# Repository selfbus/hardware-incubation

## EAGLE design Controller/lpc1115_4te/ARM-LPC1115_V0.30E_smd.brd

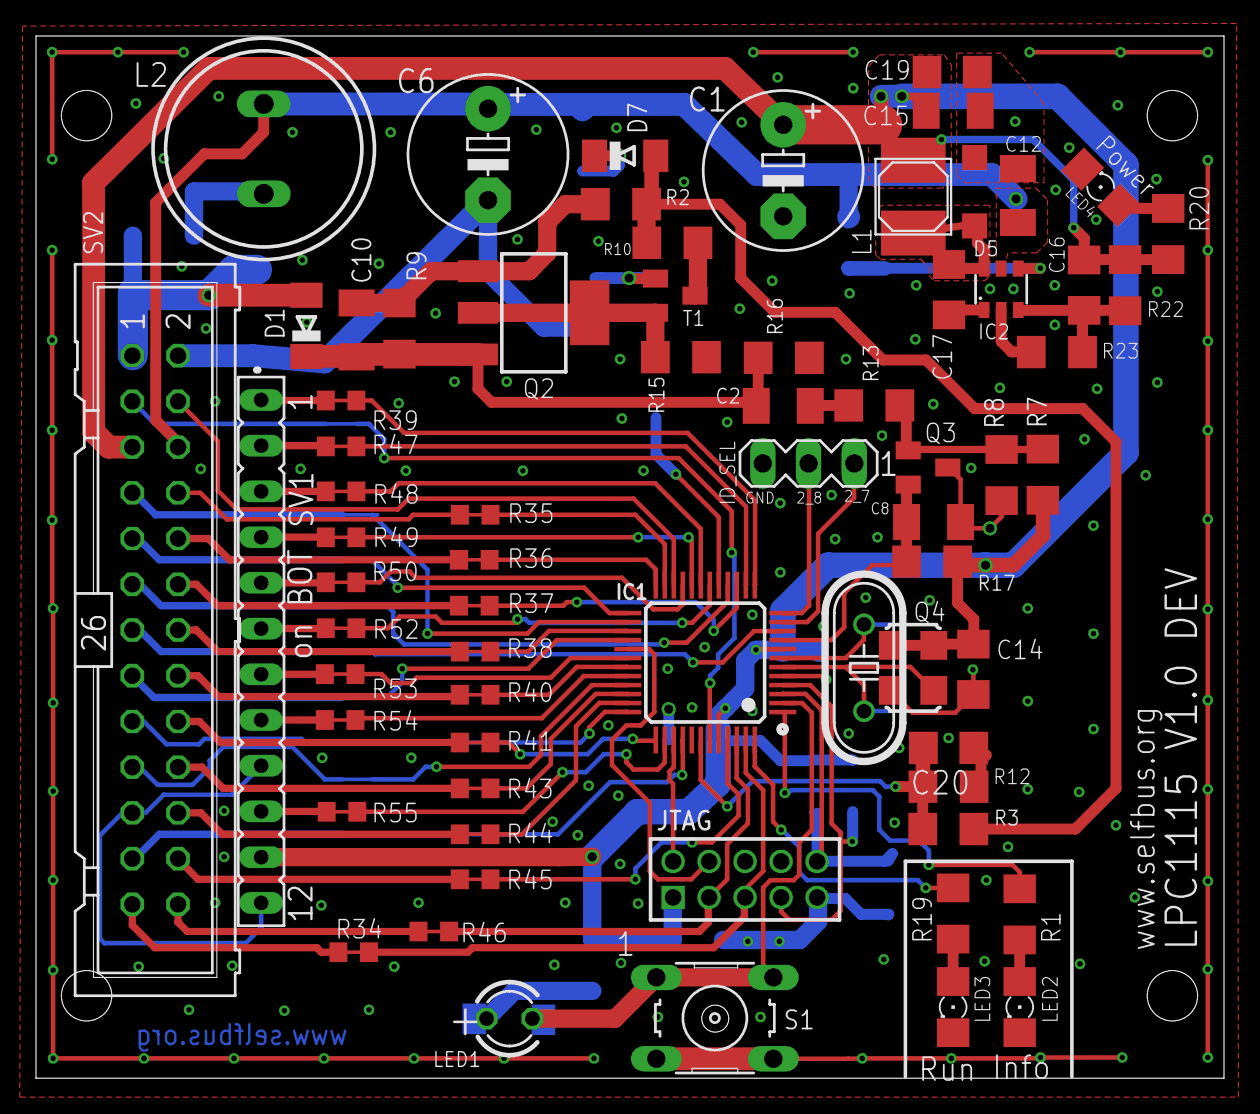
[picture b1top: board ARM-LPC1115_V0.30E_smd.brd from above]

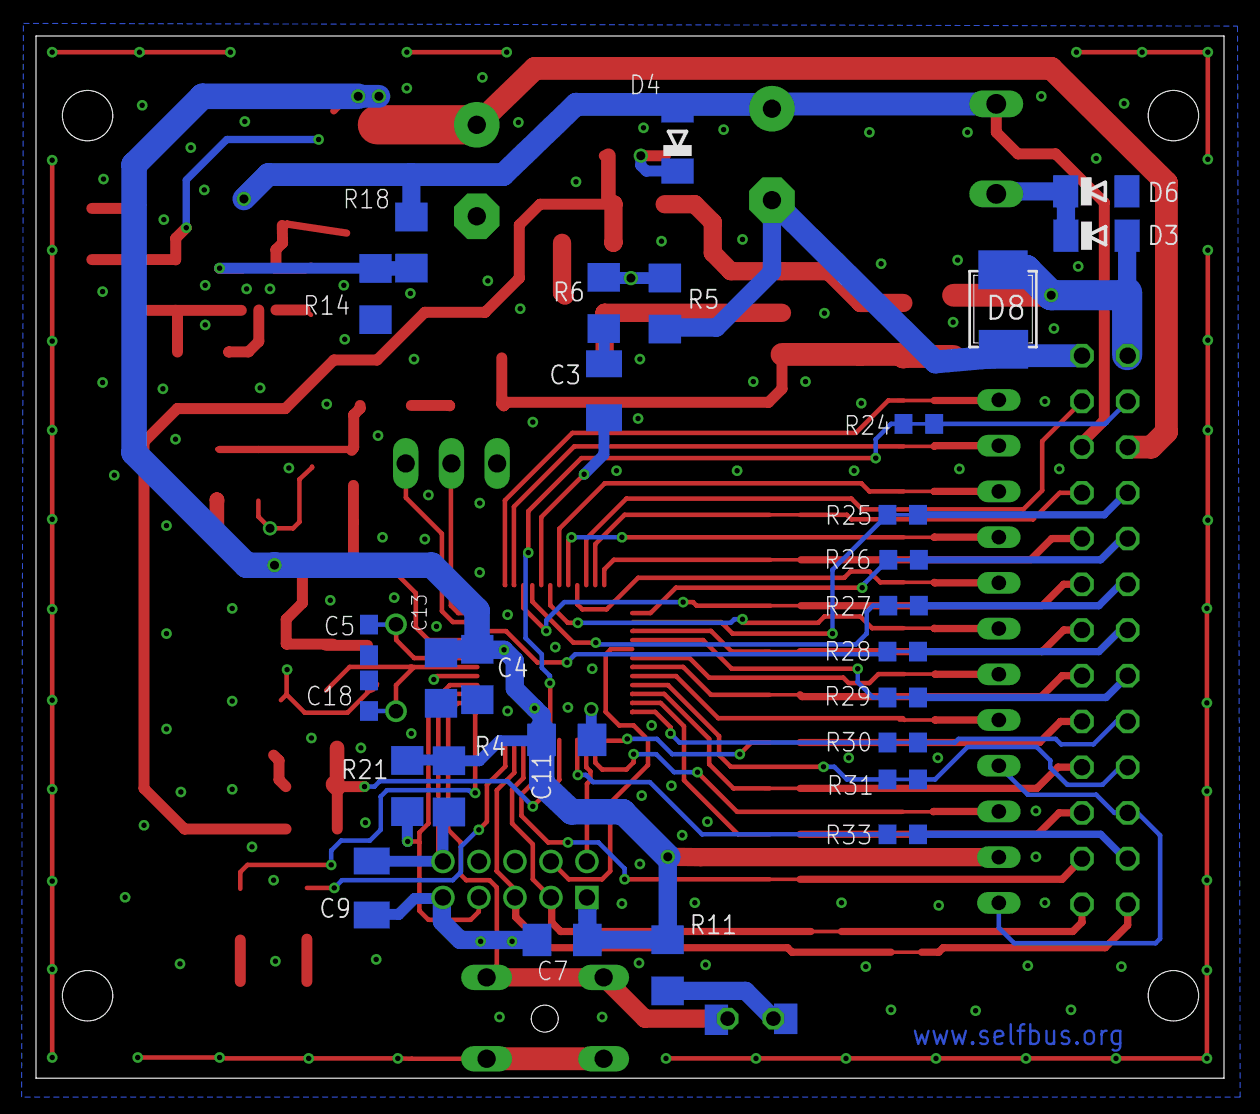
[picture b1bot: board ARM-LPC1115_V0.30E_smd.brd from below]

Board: 2 copper layers, 66.0 x 57.9 mm, 97 parts (28 on the bottom side), 96 nets.

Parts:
C1: 100µ / 10V; E5-8,5
C2: 100n; C1206K
C3, C9, C10: 10n; C1206K
C4, C14, C19: 10n; C1206
C5, C18: 18p; C0603
C6: 100µ / 50V; E5-8,5
C7, C11, C13: 100n; C1206
C8: 100p; C1206K
C12: 4.7µF/50V; C1206K
C15: 10µ / 10V; C1206K
C16: 270n; C1206
C17: 15nF; C1206
C20: 1n; C1206
D1, D3, D4, D6: 1N4148; MINIMELF
D5: RB060M-60; SOD123
D7: 7V5; MINIMELF
D8: SMB
IC1: LPC1115; LQFP48
IC2: BD9G101; SOT23-6
JTAG: J; 2X05M
L1: 6.8µH; PIS2812
L2: 150mH; SD12_1000
LED1: red; LED3MM
LED2: yellow; 1206
LED3: green; 1206
LED4: 1206
Q2: BCP52; SOT223
Q3: BC856; SOT23-BEC
Q4: 12MHz; ASF
R1, R2, R9, R11, R19, R20: 1k; R1206
R3: 91k; R1206
R4, R5, R16, R21: 100k; R1206
R6: 5k6; R1206
R7: 82k; R1206
R8: 47k; R1206
R10: 2k2; R1206
R12, R13, R17: 10k; R1206
R14: 43k; R1206
R15: 5R6; R1206
R18: 390k; R1206
R22: 2k4; R1206
R23: 680R; R1206
R24, R25, R26, R27, R28, R29, R30, R31, R33, R34, R35, R36, R37, R38, R39, R40, R41, R43, R44, R45, R46, R47, R48, R49, R50, R52, R53, R54, R55: R0603_BRIDGE
S1: Prog; B3F-10XX
SV1: LT; FE12
SV2: A; ML26
SV3: ID_SEL; MA03-1
T1: BC547C; SOT23
XTAL1: 12MHz; HC49/S

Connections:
$IO1: R25.2, SV2.7
$IO3: R26.2, SV2.9
$PWM: R24.2, SV2.3
$SDA: R27.2, SV2.11
APROG: IC1.22, SV2.4
BUS_V: C20.2, IC1.42, R3.2, R12.1
DRAIN: C2.1, C10.1, D1.C, Q2.3, R9.1, R16.2
EIB+: D1.A, D3.A, D8.1, SV2.1
EIB_DC: C6.+, C12.2, D4.A, IC2.5, L2.2, R18.1, SV2.6
EIB_IN: C8.2, IC1.9, Q3.E, R17.1
EIB_OUT: C3.2, IC1.17
GND: C1.-, C4.1, C5.1, C6.-, C7.1, C8.1, C9.1, C11.1, C12.1, C13.1, C14.2, C15.1, C18.1, C19.1, C20.1, D5.A, D6.A, D8.2, IC1.5, IC1.41, IC2.2, JTAG.9, LED2.C, LED3.C, LED4.C, Q3.C, Q4.2, R5.2, R8.1, R12.2, R14.2, R15.1, R16.1, R23.1, S1.1, S1.2, SV1.9, SV1.12, SV2.2, SV2.21, SV3.3
ID1: IC1.11, SV3.1
ID2: IC1.12, SV3.2
IO1: IC1.26, R25.1
IO2: IC1.23, R35.2
IO3: IC1.25, R26.1
IO4: IC1.24, R36.2
IO5: IC1.10, R28.1
IO6: IC1.27, R38.2
IO7: IC1.28, R29.1
IO8: IC1.31, R40.2
IO9: IC1.33, R31.1
IO10: IC1.34, R43.2
IO11: IC1.35, R44.2
IO12: IC1.40, R33.1
IO13: IC1.45, R45.2
IO14: IC1.47, JTAG.5, R34.1
IO15: IC1.46, JTAG.3, R46.2
ISP_EN: IC1.4, JTAG.7, R21.1
LT1: IC1.13, R39.1
LT2: IC1.14, R47.1
LT3: IC1.19, R48.1
LT4: IC1.20, R49.1
LT5: IC1.21, R50.1
LT6: IC1.18, R52.1
LT7: IC1.30, R53.1
LT8: IC1.32, R54.1
LT9: IC1.38, R55.1
LX: C17.1, D5.C, IC2.6, L1.P$1
unnamed: C3.1, R6.2
unnamed: C2.2, R13.1
unnamed: C5.2, IC1.7, XTAL1.1
unnamed: IC1.1, R1.2
unnamed: IC1.48, R19.2
unnamed: R10.1, T1.3
unnamed: Q2.2, R15.2, T1.2
unnamed: D3.C, D6.C, L2.1
unnamed: D4.C, D7.C
unnamed: LED2.A, R1.1
unnamed: LED3.A, R19.1
unnamed: R5.1, R6.1, T1.1
unnamed: LED4.A, R20.2
unnamed: Q3.B, R7.1, R8.2, R13.2
unnamed: C10.2, Q2.1, R2.2, R9.2
unnamed: C18.2, IC1.6, Q4.3, XTAL1.2
unnamed: C17.2, IC2.1
unnamed: IC2.4, R14.1, R18.2
unnamed: C16.1, IC2.3, R22.1, R23.2
unnamed: R28.2, SV2.13
unnamed: R29.2, SV2.15
unnamed: R30.2, SV2.17
unnamed: R31.2, SV2.19
unnamed: R33.2, SV2.23
unnamed: R34.2, SV2.25
unnamed: R35.1, SV2.8
unnamed: R36.1, SV2.10
unnamed: R37.1, SV2.12
unnamed: R38.1, SV2.14
unnamed: R40.1, SV2.16
unnamed: LED1.A, R11.1
unnamed: R41.1, SV2.18
unnamed: R43.1, SV2.20
unnamed: R44.1, SV2.22
unnamed: R45.1, SV2.24
unnamed: R46.1, SV2.26
unnamed: R39.2, SV1.1
unnamed: R47.2, SV1.2
unnamed: R48.2, SV1.3
unnamed: R49.2, SV1.4
unnamed: R50.2, SV1.5
unnamed: R52.2, SV1.6
unnamed: R53.2, SV1.7
unnamed: R54.2, SV1.8
unnamed: R55.2, SV1.10
PROG: IC1.2, LED1.K, S1.3, S1.4
PWM: IC1.43, R24.1
REF: D7.A, R2.1, R3.1, R10.2
RESET: C9.2, IC1.3, JTAG.10, R4.1
RXD: IC1.37, R41.2
SCL: IC1.15, R37.2
SDA: IC1.16, R27.1
SWCLK: IC1.29, JTAG.4
SWDIO: IC1.39, JTAG.2
TXD: IC1.36, R30.1
VCC_3V3: C1.+, C4.2, C7.2, C11.2, C13.2, C14.1, C15.2, C16.2, C19.2, IC1.8, IC1.44, JTAG.1, L1.P$2, Q4.1, Q4.4, R4.2, R7.2, R11.2, R17.2, R20.1, R21.2, R22.2, SV1.11, SV2.5

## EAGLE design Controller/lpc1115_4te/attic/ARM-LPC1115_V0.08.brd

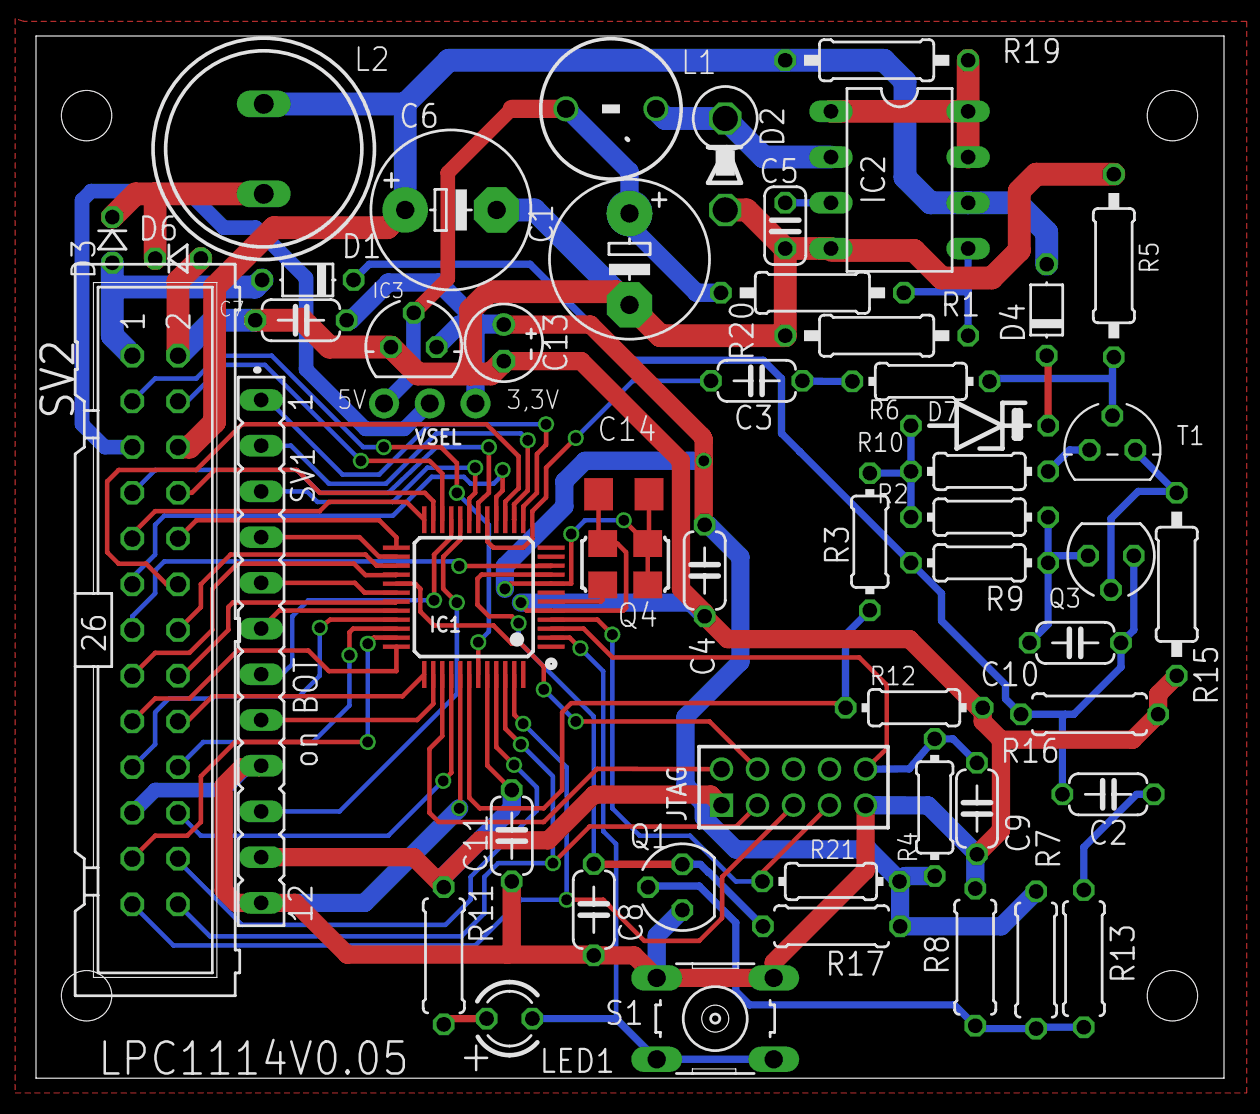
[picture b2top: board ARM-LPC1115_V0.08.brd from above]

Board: 2 copper layers, 66.0 x 57.9 mm, 53 parts (0 on the bottom side), 61 nets.

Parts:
C1, C6: 100µ; E5-8,5
C2: 100nf; C050-024X044
C3, C9, C10: 10n; C050-024X044
C4, C7, C11: 100n; C050-024X044
C5: 470p; C025-024X044
C8: 100p; C050-024X044
C13: 1µ; E2-4
C14: 10n; C1206
D1, D4: 1N4148; D-5
D2: BAT46; C1702-05
D3, D6: 1N4148; D-2.5
D7: 7,5; ZDIO-7.5
IC1: LPC1115; LQFP48
IC2: MC34063AP; DIL08
IC3: MCP1702-33; 79LXX
JTAG: J; 2X05M
L1: 220µH; L_RAD_D8RM5
L2: 150mH; SD12_1000
LED1: rot; LED3MM
Q1: BC557B; SOT54A
Q3: BC640C; SOT54D
Q4: 12MHz; ASF
R1: 1k2; 0207/10
R2, R9: 1k; 0204/7
R3: 91k; 0204/7
R4, R21: 100k; 0204/7
R5: 100k; 0207/10
R6: 5k6; 0204/7
R7: 82k; 0207/7
R8: 47k; 0207/7
R10: 2k2; 0204/7
R11: 1k; 0207/7
R12: 10k; 0204/7
R13, R17: 10k; 0207/7
R15: 5R6; 0207/10
R16: 100k; 0207/7
R19: 3R3; 0207/10
R20: 3k6; 0207/10
S1: Programmier-Taster; B3F-10XX
SV1: LT; FE12
SV2: A; ML26
T1: BC547C; TO92
VSEL: V; 1X03_ROUND

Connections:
APROG: IC1.22, SV2.4
BUS_V: IC1.42, R3.2, R12.1
DRAIN: C2.1, C10.1, D1.C, Q3.E, R9.1, R16.2
EIB+: D1.A, D3.A, SV2.1
EIB_DC: C6.+, D4.A, IC2.6, L2.2, R19.2, SV2.6
EIB_IN: C8.2, IC1.9, Q1.E, R17.1
EIB_OUT: C3.2, IC1.17
GND: C1.-, C4.1, C5.2, C6.-, C7.1, C8.1, C9.1, C11.1, C13.-, C14.2, D2.A, D6.A, IC1.5, IC1.41, IC2.4, IC3.GND, JTAG.9, Q1.C, Q4.2, R1.1, R5.2, R8.1, R12.2, R15.1, R16.1, S1.1, S1.2, SV1.9, SV1.12, SV2.2, SV2.21
IO1: IC1.18, SV2.7
IO2: IC1.23, SV2.8
IO3: IC1.24, SV2.9
IO4: IC1.25, SV2.10
IO5: IC1.10, SV2.13
IO6: IC1.27, SV2.14
IO7: IC1.28, SV2.15
IO8: IC1.31, SV2.16
IO9: IC1.33, SV2.19
IO10: IC1.34, SV2.20
IO11: IC1.40, SV2.22
IO12: IC1.35, SV2.23
IO13: IC1.45, SV2.24
IO14: IC1.47, JTAG.5, SV2.25
IO15: IC1.46, JTAG.3, SV2.26
ISP_EN: IC1.4, JTAG.7, R21.1
LT1: IC1.13, SV1.1
LT2: IC1.14, SV1.2
LT3: IC1.19, SV1.3
LT4: IC1.26, SV1.4
LT5: IC1.30, SV1.5
LT6: IC1.32, SV1.6
LT7: IC1.21, SV1.7
LT8: IC1.38, SV1.8
LT9: IC1.20, SV1.10
unnamed: C3.1, R6.2
unnamed: C2.2, R13.1
unnamed: IC2.5, R1.2, R20.1
unnamed: IC2.1, IC2.7, IC2.8, R19.1
unnamed: R10.1, T1.3
unnamed: Q3.C, R15.2, T1.1
unnamed: D3.C, D6.C, L2.1
unnamed: D4.C, D7.C
unnamed: D2.C, IC2.2, L1.1
unnamed: R5.1, R6.1, T1.2
unnamed: C5.1, IC2.3
unnamed: Q1.B, R7.1, R8.2, R13.2
unnamed: C10.2, Q3.B, R2.2, R9.2
unnamed: IC1.6, Q4.3
unnamed: LED1.A, R11.1
PROG: IC1.2, LED1.K, S1.3, S1.4
PWM: IC1.43, SV2.3
REF: D7.A, R2.1, R3.1, R10.2
RESET: C9.2, IC1.3, JTAG.10, R4.1
RXD: IC1.37, SV2.18
SCL: IC1.15, SV2.12
SDA: IC1.16, SV2.11
SWCLK: IC1.29, JTAG.4
SWDIO: IC1.39, JTAG.2
TXD: IC1.36, SV2.17
VCC_3V3: C4.2, C7.2, C11.2, C13.+, C14.1, IC1.8, IC1.44, IC3.OUT, JTAG.1, Q4.1, Q4.4, R4.2, R7.2, R11.2, R17.2, R21.2, SV1.11, VSEL.1
VCC_5V: C1.+, IC3.IN, L1.2, R20.2, VSEL.3
VCC_A: SV2.5, VSEL.2

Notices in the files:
parts and their libraries:
microbuilder: This work is placed in the public domain, and may be freely used for commercial and non-commercial work with the following conditions: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
